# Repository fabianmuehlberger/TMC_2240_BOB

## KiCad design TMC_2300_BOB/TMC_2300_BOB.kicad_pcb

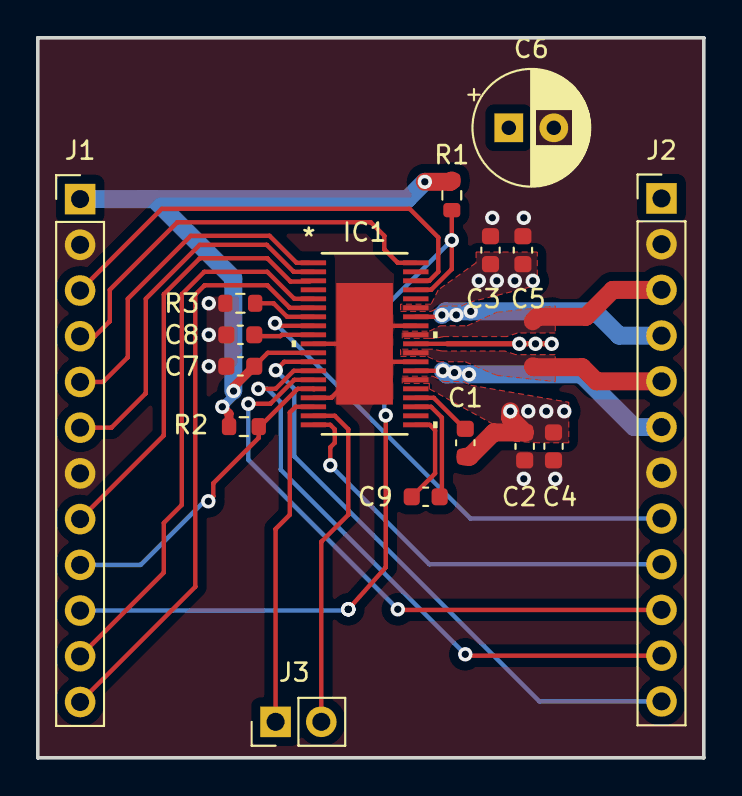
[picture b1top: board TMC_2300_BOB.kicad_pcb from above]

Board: 4 copper layers, 37.0 x 40.0 mm, 16 parts (0 on the bottom side), 28 nets.

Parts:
C1: C; C_0603_1608Metric
C2, C3, C7: 100n; C_0603_1608Metric
C4, C5: 1u; C_0603_1608Metric
C6: 47u; CP_Radial_D6.3mm_P2.50mm
C8: 2.2u; C_0603_1608Metric
C9: 22n; C_0603_1608Metric
IC1: TSSOP38_4-4X9-7_TRI
J1, J2: Conn_01x12_Socket; PinHeader_1x12_P2.54mm_Vertical
J3: Conn_01x02_Socket; PinHeader_1x02_P2.54mm_Vertical
R1, R2: 4k7; R_0603_1608Metric
R3: 12k; R_0603_1608Metric

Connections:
/A1: IC1.32 (OUT1A), J2.4
/A2: IC1.30 (OUT2A), J2.3
/AIN: IC1.8 (AIN), J2.8
/B1: IC1.26 (OUT1B), J2.6
/B2: IC1.28 (OUT2B), J2.5
/CLK16: IC1.3 (CLK), J1.8
/CSn: IC1.36 (CSN/AD2), J1.3
/DIAG1/SW: IC1.18 (DIAG1/SW), J3.2
/DIR: IC1.6 (DIR), J1.12
/DOAG0: IC1.17 (DIAG0), J3.1
/DRV_ENn: IC1.15 (DRV_ENN), J1.9, R2.2
/ENCA: IC1.14 (ENCA), J2.10
/ENCB: IC1.13 (ENCB), J2.11
/ENCN: IC1.12 (ENCN), J2.12
/MISO: IC1.2 (SDO/NAO), J1.6
/MOSI: IC1.1 (SDI/AD0), J1.5
/OV: IC1.19 (OV), J2.9
/SCK: IC1.38 (SCK/AD1), J1.4
/SLEEPn: IC1.35 (SLEEPN), J1.10, R1.2
/STEP: IC1.5 (STEP), J1.11
/VCP: C1.1, IC1.23 (VCP)
GND: C2.2, C3.2, C4.2, C5.2, C6.2, C7.2, C8.2, IC1.10 (AGND), IC1.16 (UART_EN), IC1.27 (PGND), IC1.31 (PGND), IC1.39 (GND), J1.2, J1.7, J2.2, J2.7, R3.2
unnamed: C9.2, IC1.20 (CPI)
unnamed: C9.1, IC1.22 (CPO)
unnamed: IC1.7 (IREF), R3.1
unnamed: C8.1, IC1.9 (VDD1V8)
VCC: C7.1, IC1.11 (VCC_IO), J1.1, R1.1, R2.1
Vdrive: C1.2, C2.1, C3.1, C4.1, C5.1, C6.1, IC1.25 (VS), IC1.29 (VS), IC1.33 (VS), J2.1

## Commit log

2023-09-13 Created schematic and PCB
